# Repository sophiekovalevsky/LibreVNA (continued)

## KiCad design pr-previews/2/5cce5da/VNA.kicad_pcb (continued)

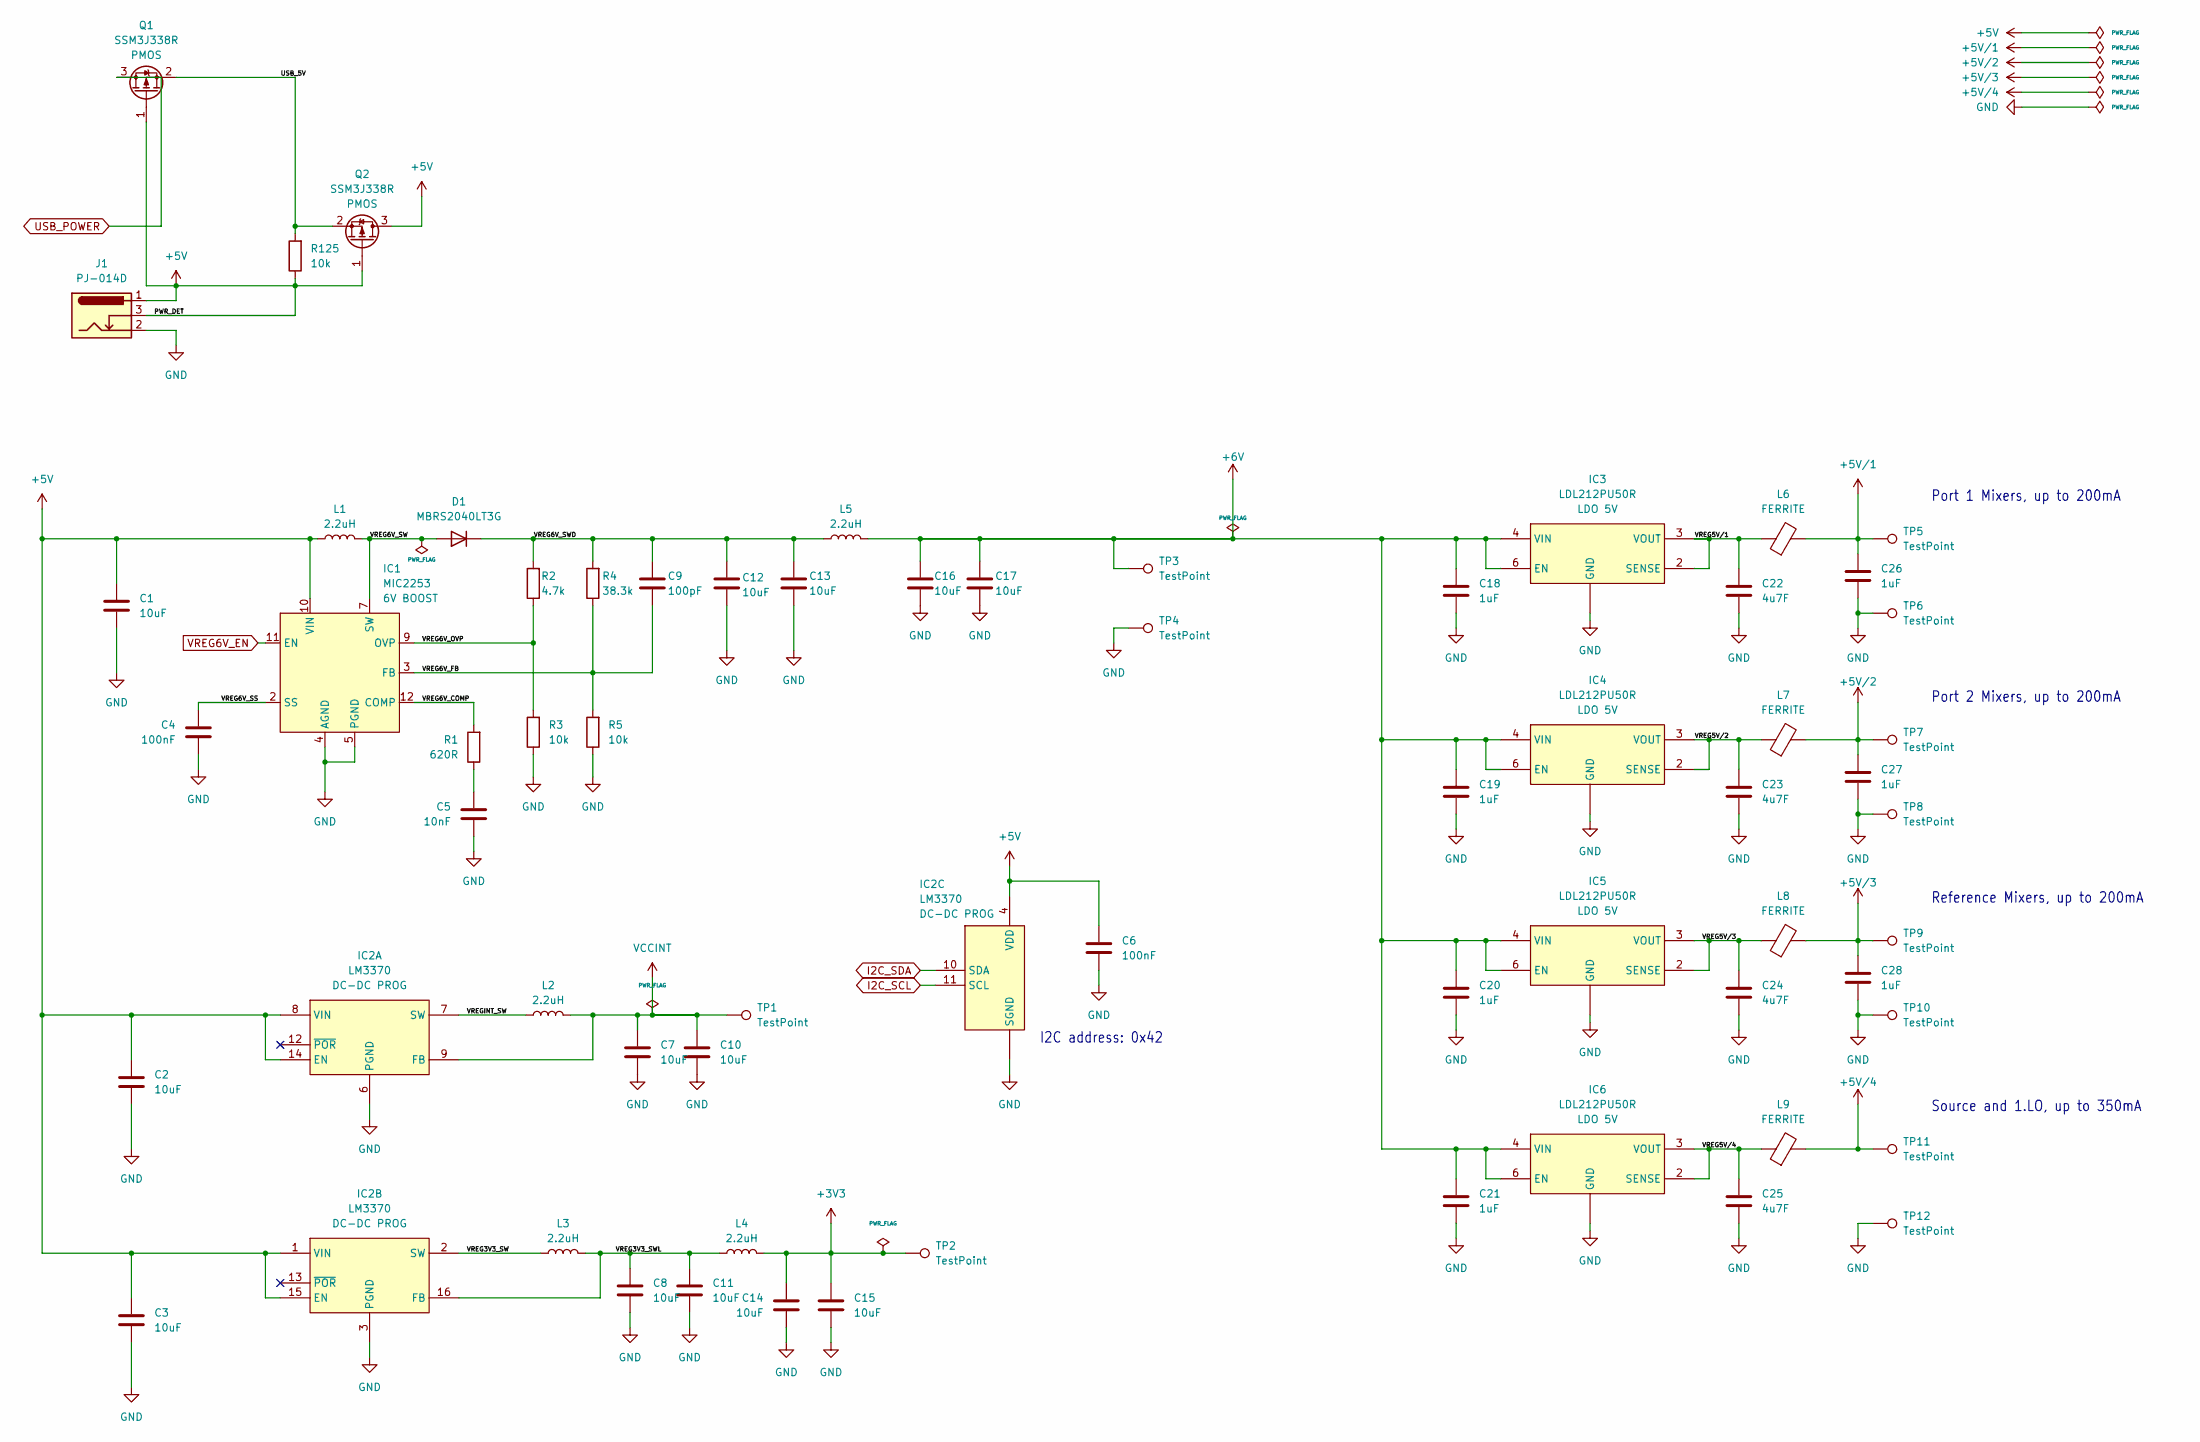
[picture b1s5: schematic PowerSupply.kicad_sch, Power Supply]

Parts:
C1, C2, C3, C7, C8, C10, C11, C12, C13, C14, C15, C16, C17: 10uF; C_1206_3216Metric
C4, C6: 100nF; C_0402_1005Metric
C5: 10nF; C_0402_1005Metric
C9: 100pF; C_0402_1005Metric
C18, C19, C20, C21, C26, C27, C28: 1uF; C_0603_1608Metric
C22, C23, C24, C25: 4u7F; C_0603_1608Metric
D1: MBRS2040LT3G; D_SMB; MPN MBRS2040LT3G
IC1: MIC2253; DFN-12-1EP_3x3mm_P0.45mm_EP1.66x2.38mm; MPN MIC2253-06YML
IC2: LM3370; DFN-16-1EP_4x5mm_P0.5mm_EP2.44x4.34mm; MPN LM3370SD-3021
IC3, IC4, IC5, IC6: LDL212PU50R; WSON-6-1EP_3x3mm_P0.95mm; MPN LDL212PU50R
J1: PJ-014D; MPN PJ-014D
L1, L2, L3, L4, L5: 2.2uH; L_Sunlord_SWPA5040S; MPN SRN5040-2R2Y
L6, L7, L8, L9: FERRITE; R_0402_1005Metric; MPN BLM15AX601SN1
Q1, Q2: SSM3J338R; SOT-23; MPN SSM3J338R
R1: 620R; R_0402_1005Metric
R2: 4.7k; R_0402_1005Metric
R3, R5, R125: 10k; R_0402_1005Metric
R4: 38.3k; R_0402_1005Metric
TP1, TP2, TP3, TP4, TP5, TP6, TP7, TP8, TP9, TP10, TP11, TP12: TestPoint; B1,27

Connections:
+3V3: C14.1, C15.1, L4.2, TP2.1; also elsewhere on the board
+5V/1: C26.2, L6.2, TP5.1; also elsewhere on the board
+5V/2: C27.2, L7.2, TP7.1; also elsewhere on the board
+5V/3: C28.2, L8.2, TP9.1; also elsewhere on the board
+5V/4: L9.2, TP11.1; also elsewhere on the board
+6V: C16.1, C17.1, C18.2, C19.2, C20.2, C21.2, IC3.4 (VIN), IC3.6 (EN), IC4.4 (VIN), IC4.6 (EN), IC5.4 (VIN), IC5.6 (EN), IC6.4 (VIN), IC6.6 (EN), L5.2, TP3.1
/Power Supply/USB_5V: Q1.2 (S), Q2.2 (S), R125.2
/Power Supply/VREG3V3_SW: IC2.2 (SW), L3.1
/Power Supply/VREG3V3_SWL: C8.1, C11.1, IC2.16 (FB), L3.2, L4.1
/Power Supply/VREG5V/1: C22.2, IC3.2 (SENSE), IC3.3 (VOUT), L6.1
/Power Supply/VREG5V/2: C23.2, IC4.2 (SENSE), IC4.3 (VOUT), L7.1
/Power Supply/VREG5V/3: C24.2, IC5.2 (SENSE), IC5.3 (VOUT), L8.1
/Power Supply/VREG5V/4: C25.2, IC6.2 (SENSE), IC6.3 (VOUT), L9.1
/Power Supply/VREG6V_COMP: IC1.12 (COMP), R1.2
/Power Supply/VREG6V_FB: C9.2, IC1.3 (FB), R4.1, R5.2
/Power Supply/VREG6V_OVP: IC1.9 (OVP), R2.1, R3.2
/Power Supply/VREG6V_SS: C4.2, IC1.2 (SS)
/Power Supply/VREG6V_SW: D1.2 (A), IC1.7 (SW), IC1.8 (SW), L1.2
/Power Supply/VREG6V_SWD: C9.1, C12.1, C13.1, D1.1 (K), L5.1, R2.2, R4.2
/Power Supply/VREGINT_SW: IC2.7 (SW), L2.1
GND: C1.2, C2.2, C3.2, C4.1, C5.1, C6.1, C7.2, C8.2, C10.2, C11.2, C12.2, C13.2, C14.2, C15.2, C16.2, C17.2, C18.1, C19.1, C20.1, C21.1, C22.1, C23.1, C24.1, C25.1, C26.1, C27.1, C28.1, IC1.4 (AGND), IC1.5 (PGND), IC1.6 (PGND), IC1.13 (PGND), IC2.3 (PGND), IC2.5 (SGND), IC2.6 (PGND), IC2.17 (SGND), IC3.1 (GND), IC3.7 (GND), IC4.1 (GND), IC4.7 (GND), IC5.1 (GND), IC5.7 (GND), IC6.1 (GND), IC6.7 (GND), J1.2, R3.1, R5.1, TP4.1, TP6.1, TP8.1, TP10.1, TP12.1; also elsewhere on the board
I2C_SCL: IC2.11 (SCL); also elsewhere on the board
I2C_SDA: IC2.10 (SDA); also elsewhere on the board
unnamed: C5.2, R1.1
USB_POWER: Q1.3 (D); also elsewhere on the board
VCCINT: C7.1, C10.1, IC2.9 (FB), L2.2, TP1.1; also elsewhere on the board
VREG6V_EN: IC1.11 (EN); also elsewhere on the board

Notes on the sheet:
Port 2 Mixers, up to 200mA
Source and 1.LO, up to 350mA
I2C address: 0x42
Port 1 Mixers, up to 200mA
Reference Mixers, up to 200mA

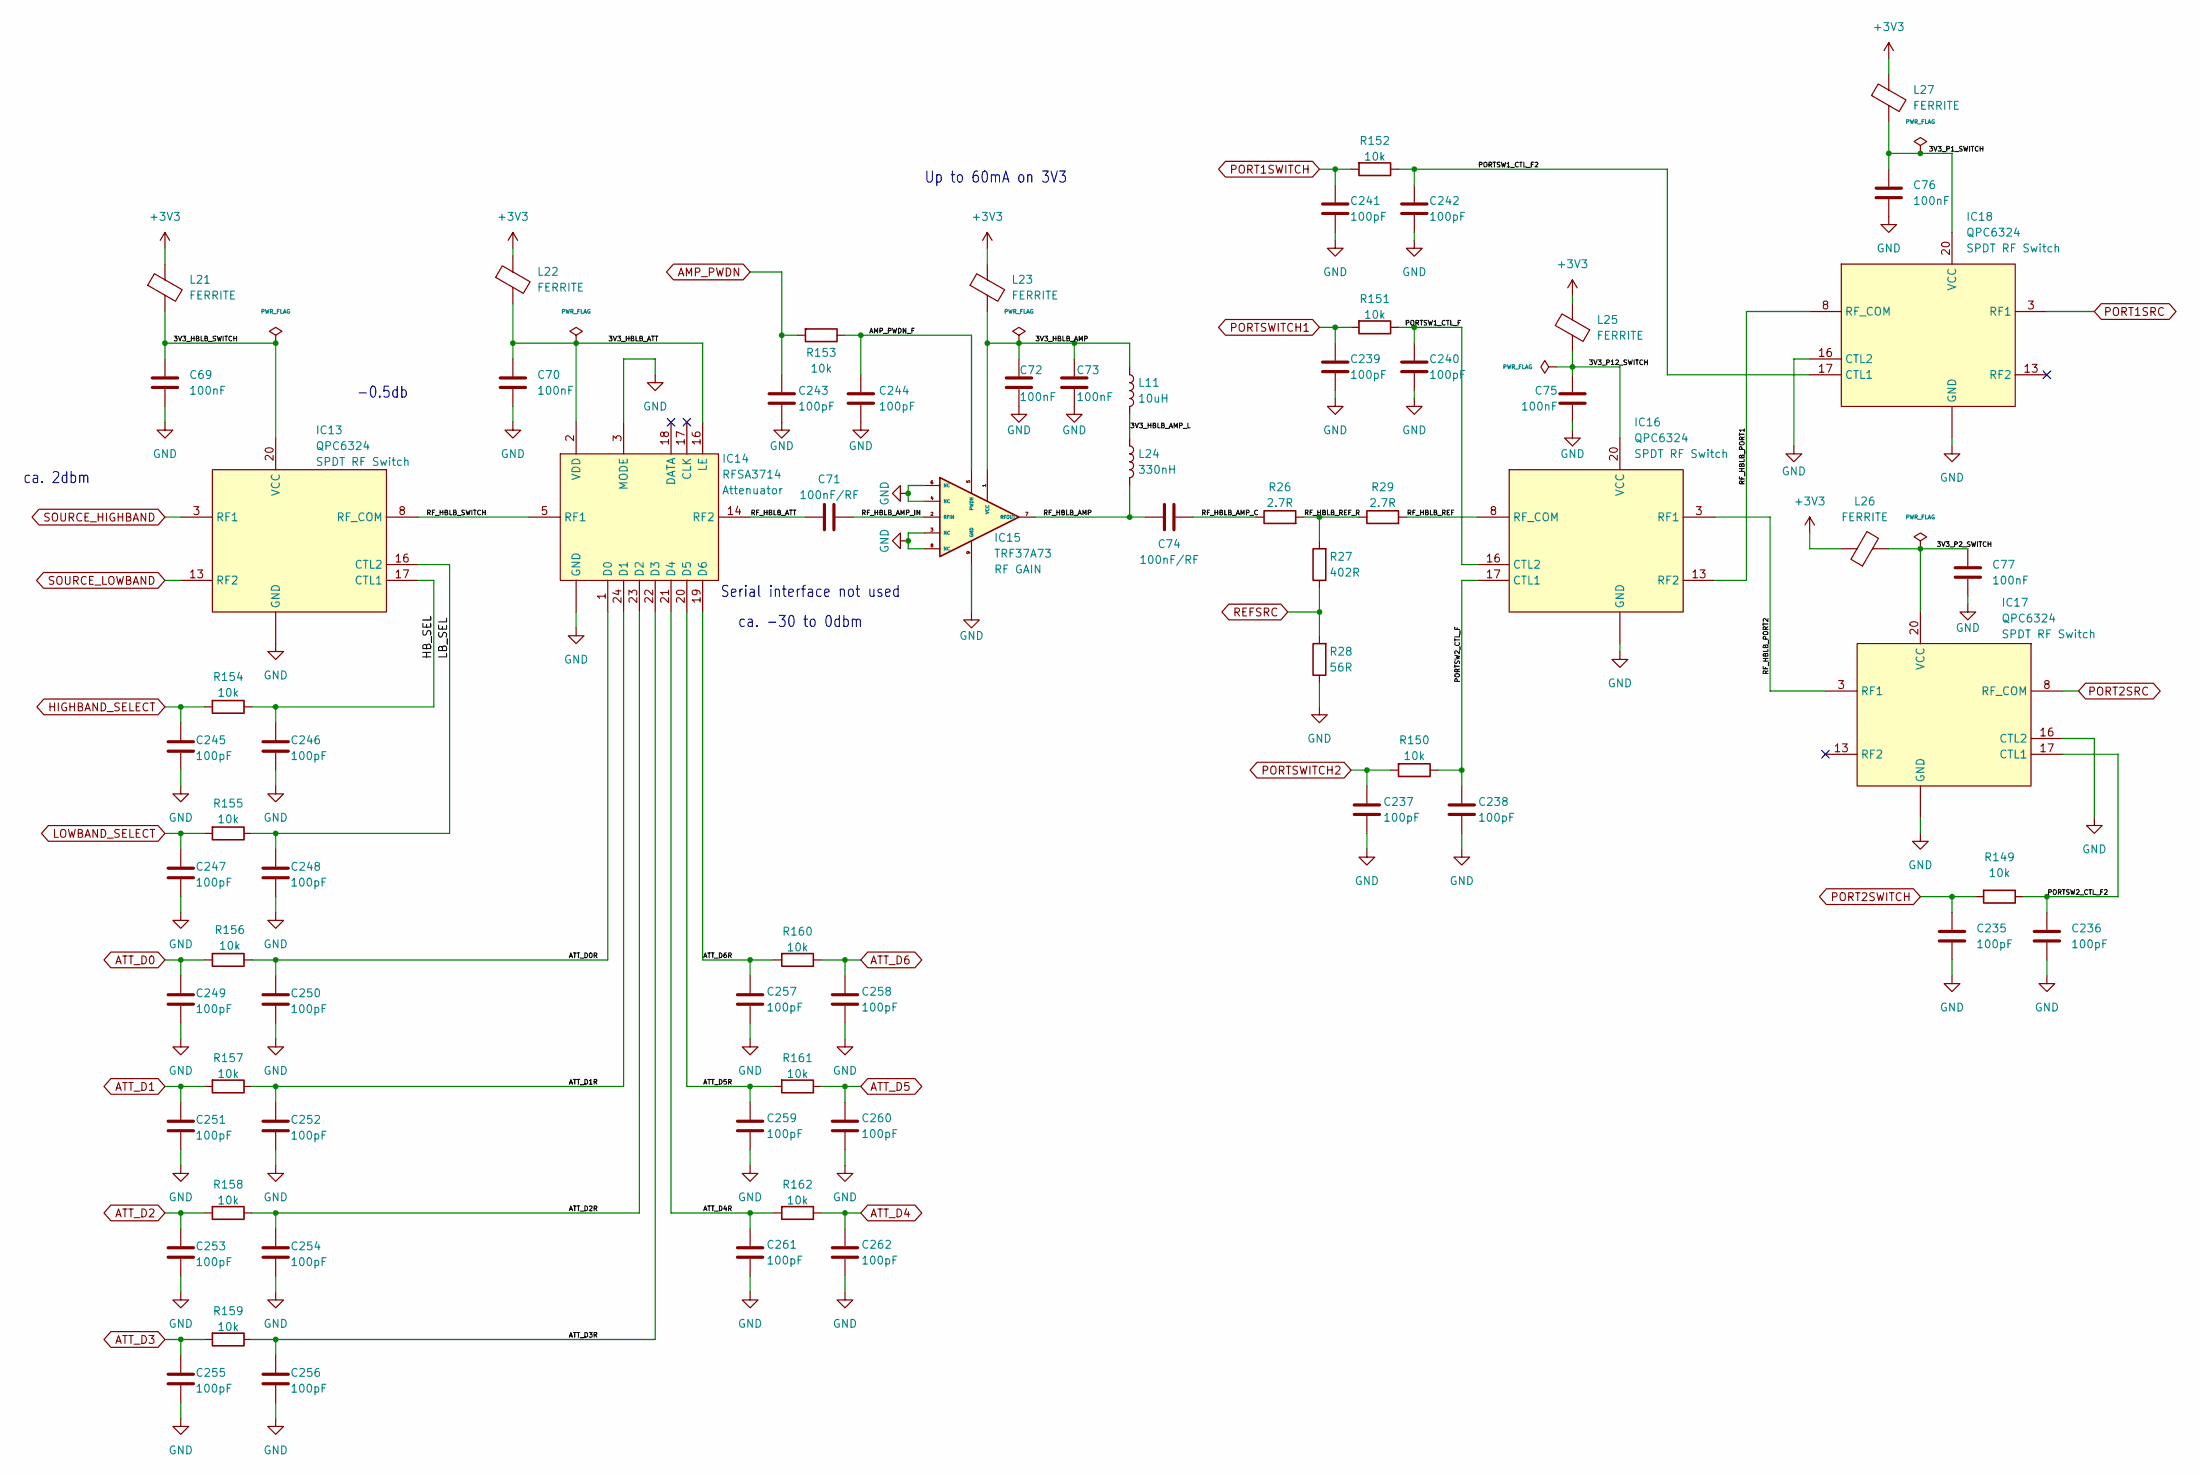
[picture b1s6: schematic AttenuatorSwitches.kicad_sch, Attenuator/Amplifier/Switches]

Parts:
C69, C70, C72, C73, C75, C76, C77: 100nF; C_0402_1005Metric
C71, C74: 100nF/RF; C_0402_1005Metric
C235, C236, C237, C238, C239, C240, C241, C242, C243, C244, C245, C246, C247, C248, C249, C250, C251, C252, C253, C254, C255, C256, C257, C258, C259, C260, C261, C262: 100pF; C_0402_1005Metric
IC13, IC16, IC17, IC18: QPC6324; QFN-20-1EP_4x4mm_P0.5mm_EP2.5x2.5mm; MPN QPC6324SR
IC14: RFSA3714; QFN-24-1EP_4x4mm_P0.5mm_EP2.6x2.6mm; MPN RFSA3714TR13
IC15: TRF37A73; DFN-8-1EP_2x2mm_P0.5mm_EP0.9x1.6mm; MPN TRF37A73IDSGR
L11: 10uH; L_0805_2012Metric_Pad1.15x1.40mm_HandSolder
L21, L22, L23, L25, L26, L27: FERRITE; R_0402_1005Metric; MPN BLM15AX601SN1
L24: 330nH; L_0402_1005Metric; MPN LQW15CNR33J10D
R26, R29: 2.7R; R_0402_1005Metric
R27: 402R; R_0402_1005Metric
R28: 56R; R_0402_1005Metric
R149, R150, R151, R152, R153, R154, R155, R156, R157, R158, R159, R160, R161, R162: 10k; R_0402_1005Metric

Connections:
+3V3: L21.1, L22.1, L23.1, L25.2, L26.1, L27.1; also elsewhere on the board
/Attenuator Amp Switches/3V3_HBLB_AMP: C72.1, C73.1, IC15.1 (VCC), L11.1, L23.2
/Attenuator Amp Switches/3V3_HBLB_AMP_L: L11.2, L24.1
/Attenuator Amp Switches/3V3_HBLB_ATT: C70.1, IC14.2 (VDD), IC14.16 (LE), L22.2
/Attenuator Amp Switches/3V3_HBLB_SWITCH: C69.1, IC13.20 (VCC), L21.2
/Attenuator Amp Switches/3V3_P1_SWITCH: C76.1, IC18.20 (VCC), L27.2
/Attenuator Amp Switches/3V3_P2_SWITCH: C77.1, IC17.20 (VCC), L26.2
/Attenuator Amp Switches/3V3_P12_SWITCH: C75.1, IC16.20 (VCC), L25.1
/Attenuator Amp Switches/AMP_PWDN_F: C244.1, IC15.5 (PWDN), R153.1
/Attenuator Amp Switches/ATT_D0R: C250.1, IC14.1 (D0), R156.1
/Attenuator Amp Switches/ATT_D1R: C252.1, IC14.24 (D1), R157.1
/Attenuator Amp Switches/ATT_D2R: C254.1, IC14.23 (D2), R158.1
/Attenuator Amp Switches/ATT_D3R: C256.1, IC14.22 (D3), R159.1
/Attenuator Amp Switches/ATT_D4R: C261.1, IC14.21 (D4), R162.2
/Attenuator Amp Switches/ATT_D5R: C259.1, IC14.20 (D5), R161.2
/Attenuator Amp Switches/ATT_D6R: C257.1, IC14.19 (D6), R160.2
/Attenuator Amp Switches/HB_SEL: C246.1, IC13.17 (CTL1), R154.1
/Attenuator Amp Switches/LB_SEL: C248.1, IC13.16 (CTL2), R155.1
/Attenuator Amp Switches/PORTSW1_CTL_F: C240.1, IC16.16 (CTL2), R151.1
/Attenuator Amp Switches/PORTSW1_CTL_F2: C242.1, IC18.17 (CTL1), R152.1
/Attenuator Amp Switches/PORTSW2_CTL_F: C238.1, IC16.17 (CTL1), R150.1
/Attenuator Amp Switches/PORTSW2_CTL_F2: C236.1, IC17.17 (CTL1), R149.1
/Attenuator Amp Switches/RF_HBLB_AMP: C74.1, IC15.7 (RFOUT), L24.2
/Attenuator Amp Switches/RF_HBLB_AMP_C: C74.2, R26.1
/Attenuator Amp Switches/RF_HBLB_AMP_IN: C71.2, IC15.2 (RFIN)
/Attenuator Amp Switches/RF_HBLB_ATT: C71.1, IC14.14 (RF2)
/Attenuator Amp Switches/RF_HBLB_PORT1: IC16.13 (RF2), IC18.8 (RF_COM)
/Attenuator Amp Switches/RF_HBLB_PORT2: IC16.3 (RF1), IC17.3 (RF1)
/Attenuator Amp Switches/RF_HBLB_REF: IC16.8 (RF_COM), R29.2
/Attenuator Amp Switches/RF_HBLB_REF_R: R26.2, R27.2, R29.1
/Attenuator Amp Switches/RF_HBLB_SWITCH: IC13.8 (RF_COM), IC14.5 (RF1)
AMP_PWDN: C243.1, R153.2; also elsewhere on the board
ATT_D0: C249.1, R156.2; also elsewhere on the board
ATT_D1: C251.1, R157.2; also elsewhere on the board
ATT_D2: C253.1, R158.2; also elsewhere on the board
ATT_D3: C255.1, R159.2; also elsewhere on the board
ATT_D4: C262.1, R162.1; also elsewhere on the board
ATT_D5: C260.1, R161.1; also elsewhere on the board
ATT_D6: C258.1, R160.1; also elsewhere on the board
GND: C69.2, C70.2, C72.2, C73.2, C75.2, C76.2, C77.2, C235.2, C236.2, C237.2, C238.2, C239.2, C240.2, C241.2, C242.2, C243.2, C244.2, C245.2, C246.2, C247.2, C248.2, C249.2, C250.2, C251.2, C252.2, C253.2, C254.2, C255.2, C256.2, C257.2, C258.2, C259.2, C260.2, C261.2, C262.2, IC13.1 (GND), IC13.2 (GND), IC13.4 (GND), IC13.5 (GND), IC13.6 (GND), IC13.7 (GND), IC13.9 (GND), IC13.10 (GND), IC13.11 (GND), IC13.12 (GND), IC13.14 (GND), IC13.15 (GND), IC13.18 (GND), IC13.19 (GND), IC13.21 (GND), IC14.3 (MODE), IC14.4 (GND), IC14.6 (GND), IC14.7 (GND), IC14.8 (GND), IC14.9 (GND), IC14.10 (GND), IC14.11 (GND), IC14.12 (GND), IC14.13 (GND), IC14.15 (GND), IC14.25 (GND), IC15.3 (NC), IC15.4 (NC), IC15.6 (NC), IC15.8 (NC), IC15.9 (GND), IC16.1 (GND), IC16.2 (GND), IC16.4 (GND), IC16.5 (GND), IC16.6 (GND), IC16.7 (GND), IC16.9 (GND), IC16.10 (GND), IC16.11 (GND), IC16.12 (GND), IC16.14 (GND), IC16.15 (GND), IC16.18 (GND), IC16.19 (GND), IC16.21 (GND), IC17.1 (GND), IC17.2 (GND), IC17.4 (GND), IC17.5 (GND), IC17.6 (GND), IC17.7 (GND), IC17.9 (GND), IC17.10 (GND), IC17.11 (GND), IC17.12 (GND), IC17.14 (GND), IC17.15 (GND), IC17.16 (CTL2), IC17.18 (GND), IC17.19 (GND), IC17.21 (GND), IC18.1 (GND), IC18.2 (GND), IC18.4 (GND), IC18.5 (GND), IC18.6 (GND), IC18.7 (GND), IC18.9 (GND), IC18.10 (GND), IC18.11 (GND), IC18.12 (GND), IC18.14 (GND), IC18.15 (GND), IC18.16 (CTL2), IC18.18 (GND), IC18.19 (GND), IC18.21 (GND), R28.1; also elsewhere on the board
HIGHBAND_SELECT: C245.1, R154.2; also elsewhere on the board
LOWBAND_SELECT: C247.1, R155.2; also elsewhere on the board
PORT1SRC: IC18.3 (RF1); also elsewhere on the board
PORT1SWITCH: C241.1, R152.2; also elsewhere on the board
PORT2SRC: IC17.8 (RF_COM); also elsewhere on the board
PORT2SWITCH: C235.1, R149.2; also elsewhere on the board
PORTSWITCH1: C239.1, R151.2; also elsewhere on the board
PORTSWITCH2: C237.1, R150.2; also elsewhere on the board
REFSRC: R27.1, R28.2; also elsewhere on the board
SOURCE_HIGHBAND: IC13.3 (RF1); also elsewhere on the board
SOURCE_LOWBAND: IC13.13 (RF2); also elsewhere on the board

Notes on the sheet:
ca. 2dbm
-0.5db
Up to 60mA on 3V3
ca. -30 to 0dbm
Serial interface not used

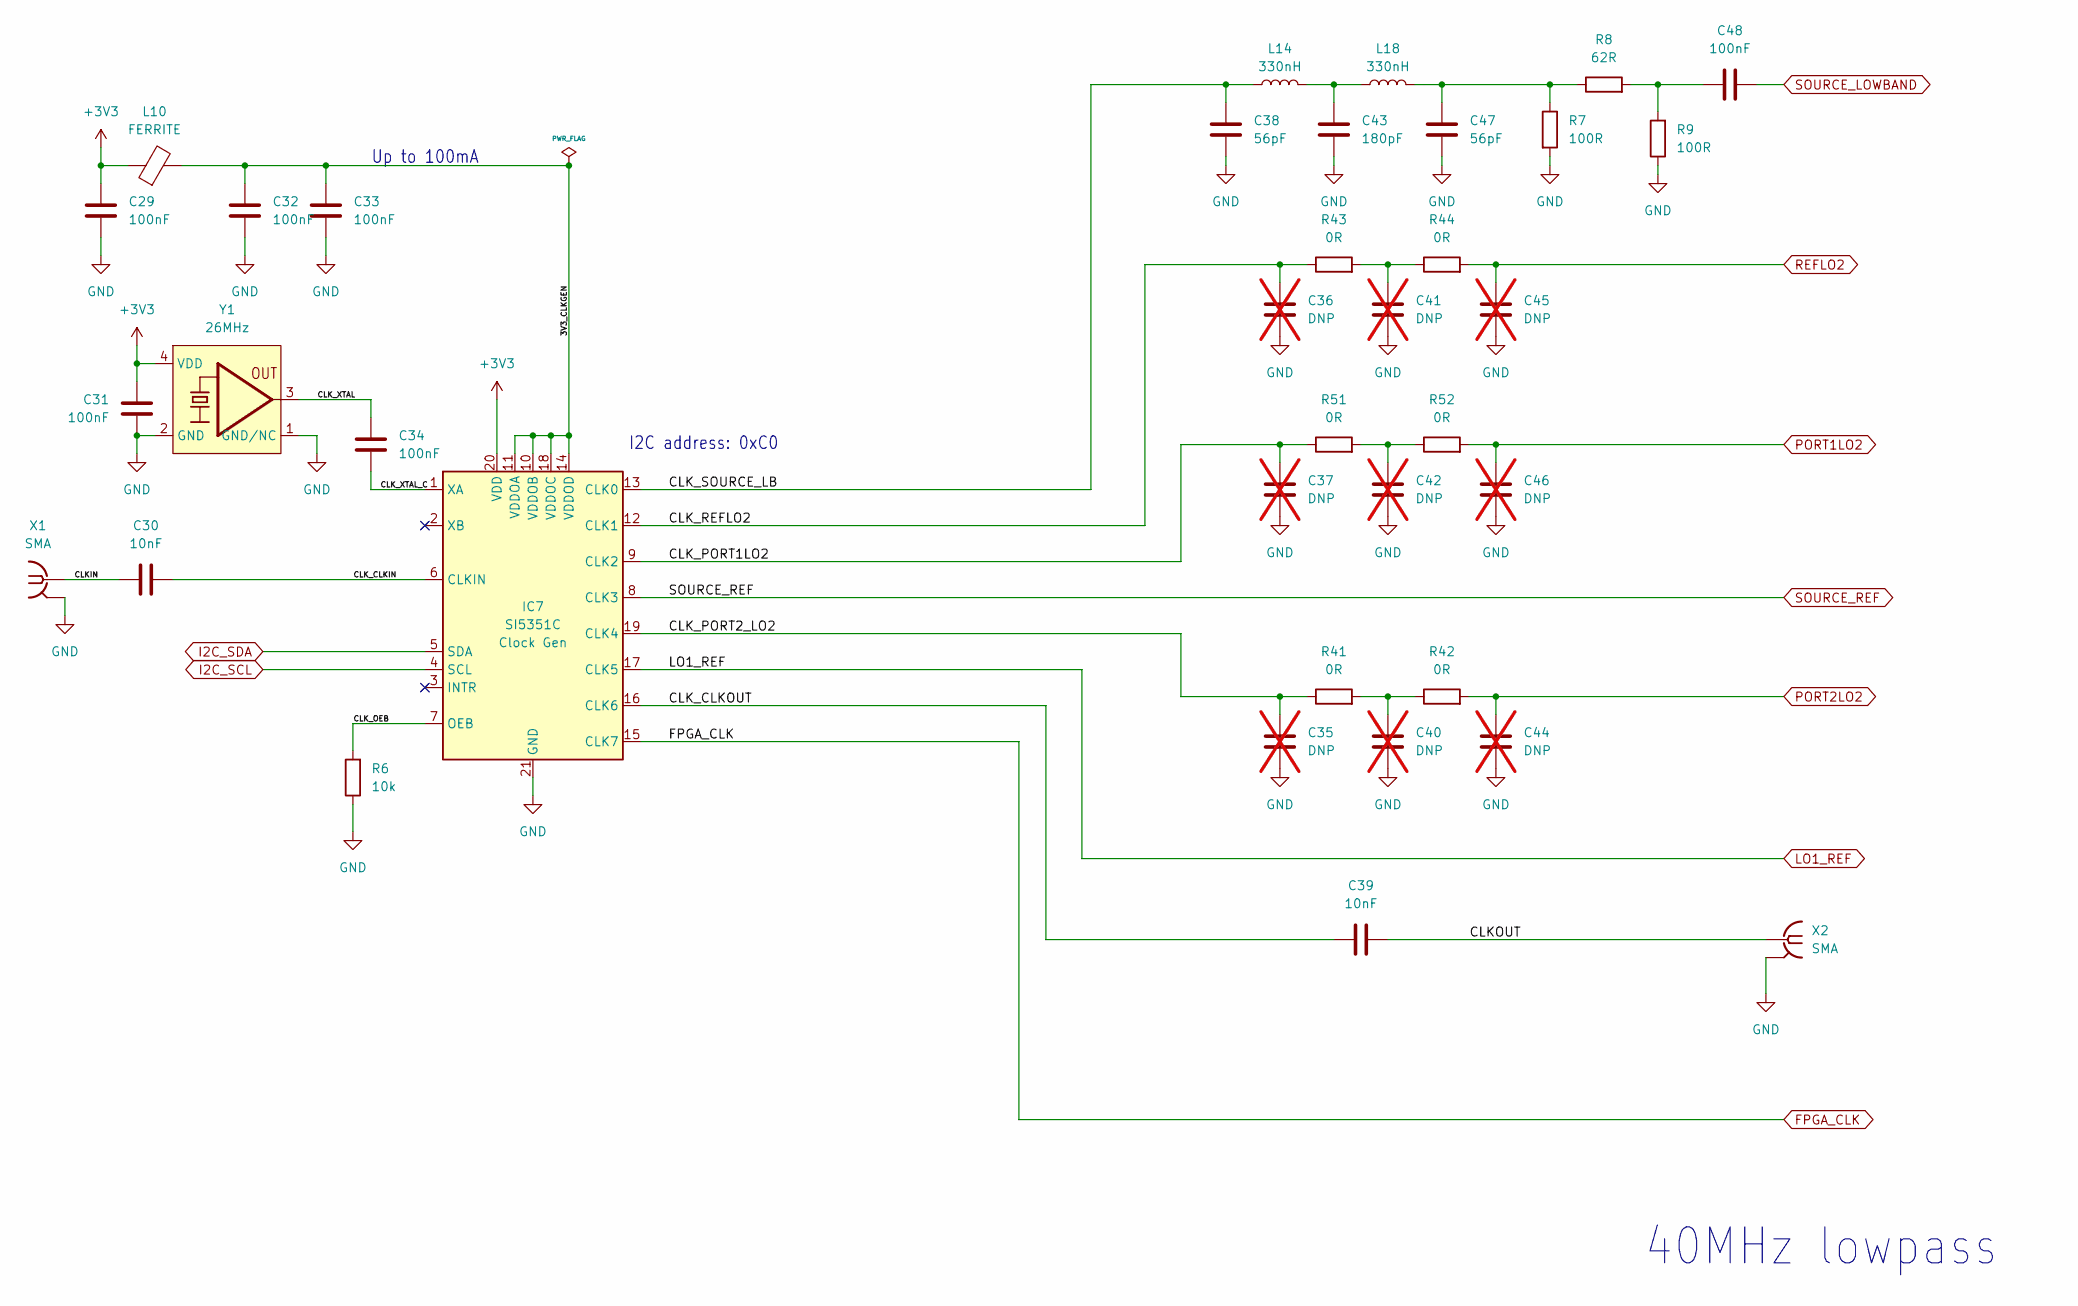
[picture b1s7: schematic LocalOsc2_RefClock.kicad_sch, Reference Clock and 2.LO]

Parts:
C29, C31, C32, C33, C34, C48: 100nF; C_0402_1005Metric
C30, C39: 10nF; C_0402_1005Metric
C35, C36, C37, C40, C41, C42, C44, C45, C46: DNP; C_0402_1005Metric; not fitted
C38, C47: 56pF; C_0402_1005Metric
C43: 180pF; C_0402_1005Metric
IC7: SI5351C; QFN-20-1EP_4x4mm_P0.5mm_EP2.7x2.7mm; MPN SI5351C-B-GM
L10: FERRITE; R_0402_1005Metric; MPN BLM15AX601SN1
L14, L18: 330nH; L_0402_1005Metric; MPN LQW15CNR33J10D
R6: 10k; R_0402_1005Metric
R7, R9: 100R; R_0402_1005Metric
R8: 62R; R_0402_1005Metric
R41, R42, R43, R44, R51, R52: 0R; R_0402_1005Metric
X1, X2: SMA; J502-ND-142-0711-821_826
Y1: 26MHz; Oscillator_SMD_ECS_20CSMV4_2.0x1.6mm; MPN ECS-TXO-20CSMV4-260-AN-TR

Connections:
+3V3: C29.2, C31.2, IC7.20 (VDD), L10.1, Y1.4 (VDD); also elsewhere on the board
/2.LO + Ref Clock/3V3_CLKGEN: C32.2, C33.2, IC7.10 (VDDOB), IC7.11 (VDDOA), IC7.14 (VDDOD), IC7.18 (VDDOC), L10.2
/2.LO + Ref Clock/CLKIN: C30.1, X1.1
/2.LO + Ref Clock/CLKOUT: C39.2, X2.1
/2.LO + Ref Clock/CLK_CLKIN: C30.2, IC7.6 (CLKIN)
/2.LO + Ref Clock/CLK_CLKOUT: C39.1, IC7.16 (CLK6)
/2.LO + Ref Clock/CLK_OEB: IC7.7 (OEB), R6.2
/2.LO + Ref Clock/CLK_PORT1LO2: C37.1, IC7.9 (CLK2), R51.1
/2.LO + Ref Clock/CLK_PORT2_LO2: C35.1, IC7.19 (CLK4), R41.1
/2.LO + Ref Clock/CLK_REFLO2: C36.1, IC7.12 (CLK1), R43.1
/2.LO + Ref Clock/CLK_SOURCE_LB: C38.1, IC7.13 (CLK0), L14.1
/2.LO + Ref Clock/CLK_XTAL: C34.2, Y1.3 (OUT)
/2.LO + Ref Clock/CLK_XTAL_C: C34.1, IC7.1 (XA)
FPGA_CLK: IC7.15 (CLK7); also elsewhere on the board
GND: C29.1, C31.1, C32.1, C33.1, C35.2, C36.2, C37.2, C38.2, C40.2, C41.2, C42.2, C43.2, C44.2, C45.2, C46.2, C47.2, IC7.21 (GND), R6.1, R7.2, R9.1, X1.G@1 (2), X1.G@2 (2), X1.G@3 (2), X1.G@4 (2), X2.G@1 (2), X2.G@2 (2), X2.G@3 (2), X2.G@4 (2), Y1.1 (GND/NC), Y1.2 (GND); also elsewhere on the board
I2C_SCL: IC7.4 (SCL); also elsewhere on the board
I2C_SDA: IC7.5 (SDA); also elsewhere on the board
LO1_REF: IC7.17 (CLK5); also elsewhere on the board
unnamed: C40.1, R41.2, R42.1
unnamed: C41.1, R43.2, R44.1
unnamed: C42.1, R51.2, R52.1
unnamed: C43.1, L14.2, L18.1
unnamed: C47.1, L18.2, R7.1, R8.1
unnamed: C48.2, R8.2, R9.2
PORT1LO2: C46.1, R52.2; also elsewhere on the board
PORT2LO2: C44.1, R42.2; also elsewhere on the board
REFLO2: C45.1, R44.2; also elsewhere on the board
SOURCE_LOWBAND: C48.1; also elsewhere on the board
SOURCE_REF: IC7.8 (CLK3); also elsewhere on the board

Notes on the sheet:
I2C address: 0xC0
40MHz lowpass
Up to 100mA

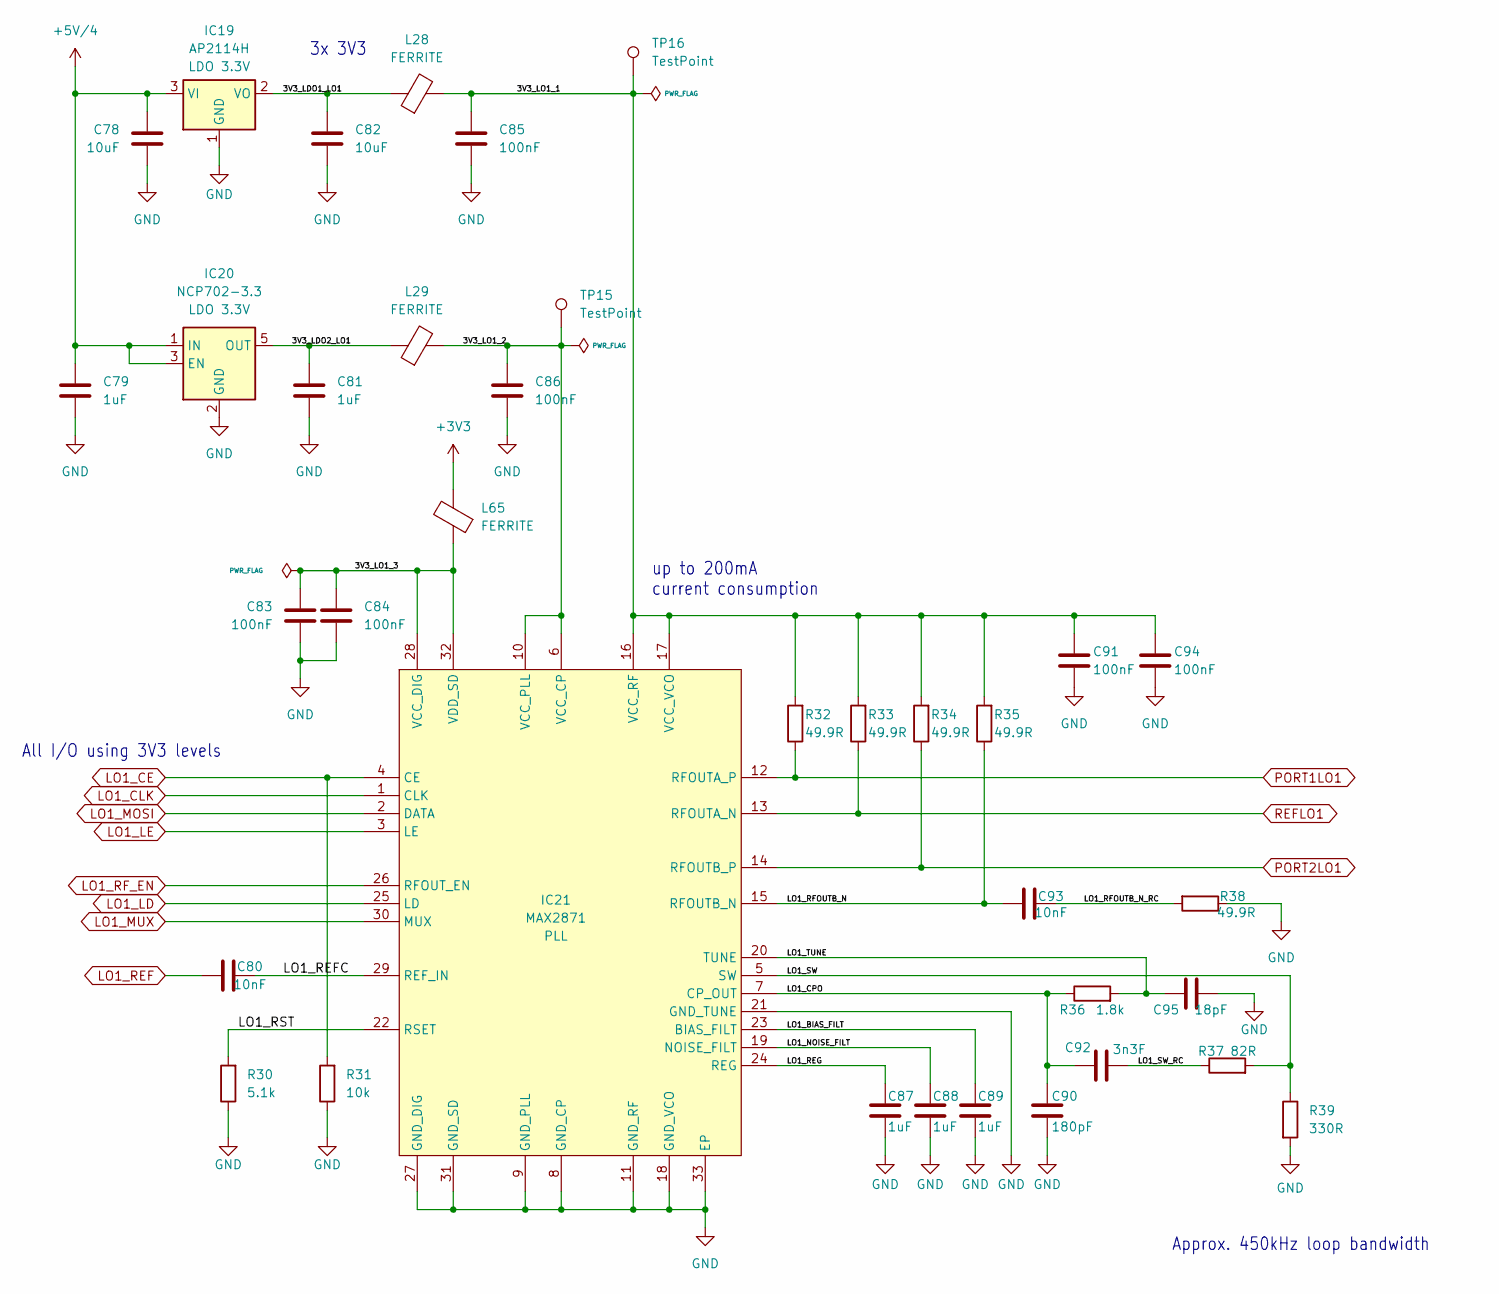
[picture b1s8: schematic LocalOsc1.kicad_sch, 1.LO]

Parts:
C78, C82: 10uF; C_1206_3216Metric
C79, C81: 1uF; C_0603_1608Metric
C80, C93: 10nF; C_0402_1005Metric
C83, C84, C85, C86, C91, C94: 100nF; C_0402_1005Metric
C87, C88, C89: 1uF; C_0402_1005Metric
C90: 180pF; C_0402_1005Metric
C92: 3n3F; C_0402_1005Metric
C95: 18pF; C_0402_1005Metric
IC19: AP2114H; SOT-223-3_TabPin2; MPN AP2114H-3.3TRG1
IC20: NCP702-3.3; SOT-23-5; MPN NCP702SN33T1G
IC21: MAX2871; QFN-32-1EP_5x5mm_P0.5mm_EP3.1x3.1mm; MPN MAX2871ETJ+
L28, L29, L65: FERRITE; R_0402_1005Metric; MPN BLM15AX601SN1
R30: 5.1k; R_0402_1005Metric
R31: 10k; R_0402_1005Metric
R32, R33, R34, R35, R38: 49.9R; R_0402_1005Metric
R36: 1.8k; R_0402_1005Metric
R37: 82R; R_0402_1005Metric
R39: 330R; R_0402_1005Metric
TP15, TP16: TestPoint; B1,27

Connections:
+3V3: L65.2; also elsewhere on the board
+5V/4: C78.1, C79.1, IC19.3 (VI), IC20.1 (IN), IC20.3 (EN); also elsewhere on the board
/1.LO/3V3_LDO1_LO1: C82.1, IC19.2 (VO), L28.1
/1.LO/3V3_LDO2_LO1: C81.1, IC20.5 (OUT), L29.1
/1.LO/3V3_LO1_1: C85.1, C91.1, C94.1, IC21.16 (VCC_RF), IC21.17 (VCC_VCO), L28.2, R32.2, R33.2, R34.2, R35.2, TP16.1
/1.LO/3V3_LO1_2: C86.1, IC21.6 (VCC_CP), IC21.10 (VCC_PLL), L29.2, TP15.1
/1.LO/3V3_LO1_3: C83.1, C84.1, IC21.28 (VCC_DIG), IC21.32 (VDD_SD), L65.1
/1.LO/LO1_BIAS_FILT: C89.1, IC21.23 (BIAS_FILT)
/1.LO/LO1_CPO: C90.1, C92.2, IC21.7 (CP_OUT), R36.1
/1.LO/LO1_NOISE_FILT: C88.1, IC21.19 (NOISE_FILT)
/1.LO/LO1_REFC: C80.2, IC21.29 (REF_IN)
/1.LO/LO1_REG: C87.1, IC21.24 (REG)
/1.LO/LO1_RFOUTB_N: C93.2, IC21.15 (RFOUTB_N), R35.1
/1.LO/LO1_RFOUTB_N_RC: C93.1, R38.2
/1.LO/LO1_RST: IC21.22 (RSET), R30.2
/1.LO/LO1_SW: IC21.5 (SW), R37.2, R39.1
/1.LO/LO1_SW_RC: C92.1, R37.1
/1.LO/LO1_TUNE: C95.2, IC21.20 (TUNE), R36.2
GND: C78.2, C79.2, C81.2, C82.2, C83.2, C84.2, C85.2, C86.2, C87.2, C88.2, C89.2, C90.2, C91.2, C94.2, C95.1, IC19.1 (GND), IC20.2 (GND), IC21.8 (GND_CP), IC21.9 (GND_PLL), IC21.11 (GND_RF), IC21.18 (GND_VCO), IC21.21 (GND_TUNE), IC21.27 (GND_DIG), IC21.31 (GND_SD), IC21.33 (EP), R30.1, R31.1, R38.1, R39.2; also elsewhere on the board
LO1_CE: IC21.4 (CE), R31.2; also elsewhere on the board
LO1_CLK: IC21.1 (CLK); also elsewhere on the board
LO1_LD: IC21.25 (LD); also elsewhere on the board
LO1_LE: IC21.3 (LE); also elsewhere on the board
LO1_MOSI: IC21.2 (DATA); also elsewhere on the board
LO1_MUX: IC21.30 (MUX); also elsewhere on the board
LO1_REF: C80.1; also elsewhere on the board
LO1_RF_EN: IC21.26 (RFOUT_EN); also elsewhere on the board
PORT1LO1: IC21.12 (RFOUTA_P), R32.1; also elsewhere on the board
PORT2LO1: IC21.14 (RFOUTB_P), R34.1; also elsewhere on the board
REFLO1: IC21.13 (RFOUTA_N), R33.1; also elsewhere on the board

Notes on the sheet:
All I/O using 3V3 levels
up to 200mA current consumption
3x 3V3
Approx. 450kHz loop bandwidth

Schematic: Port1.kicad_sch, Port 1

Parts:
C96, C99, C109, C110: 100nF/RF; C_0402_1005Metric
C97, C98, C102, C103, C114, C115, C116, C117, C118, C119, C122, C132, C269: 100nF; C_0402_1005Metric
C100, C101, C108, C129, C131: 1uF; C_0402_1005Metric
C104, C105, C106, C111, C120, C123: 10nF; C_0402_1005Metric
C107, C112, C113: DNP; C_0402_1005Metric; not fitted
C121, C125, C126, C127: 330pF; C_0402_1005Metric
C124: 120pF; C_0402_1005Metric
C128: 150pF; C_0402_1005Metric
C130: 33pF; C_0402_1005Metric
IC22: LT5560; WSON-8-1EP_3x3mm_P0.5mm_EP1.45x2.4mm; MPN LT5560EDD
IC23: THS4521IDGKR; VSSOP-8_3.0x3.0mm_P0.65mm; MPN THS4521IDGKR
IC24: ADL5801; QFN-24-1EP_4x4mm_P0.5mm_EP2.6x2.6mm; MPN ADL5801
IC25: NCP702-1.8; SOT-23-5; MPN NCP702SN18T1G
IC26: MCP33131D-10-E/MS; VSSOP-10_3x3mm_P0.5mm; MPN MCP33131D-10-E/MS
J2: SMA; BU-1420701851; MPN AMPHENOL-132289
L12, L13, L15, L16, L17: FERRITE; R_0402_1005Metric; MPN BLM15AX601SN1
L30, L31, L32, L33: 330nH; L_0402_1005Metric; MPN LQW15CNR33J10D
L34, L35: 68nH; L_0402_1005Metric; MPN LQW15AN68NJ00D
L36, L37: 33nH; L_0402_1005Metric; MPN LQW15AN33NJ00D
R45, R46, R50: 49.9R; R_0402_1005Metric
R48: PAT0816-C-3DB-T5; PAT0816; not fitted
R49: PAT0816-C-3DB-T5; PAT0816
R53, R54, R58, R59, R61, R62: 220R; R_0402_1005Metric
R55, R56: 6.8k; R_0402_1005Metric
R57: DNP; R_0402_1005Metric; not fitted
R60: 1k; R_0402_1005Metric
R63, R66: 56R; R_0402_1005Metric
R64, R65: 20R; R_0402_1005Metric
R74, R75: 100R; R_0402_1005Metric
R168: 75R; R_0402_1005Metric
T1: B012-617DB-1-63-B331; EASTEVER_BALUN; MPN B012-617DB-1-63-B331
TP17: TestPoint; B1,27

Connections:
+3V3: C132.2, IC26.9 (SDI), IC26.10 (DVIO); also elsewhere on the board
+5V/1: L12.2, L13.2, L15.2, L16.2, L17.2, R60.1; also elsewhere on the board
/Port 1/RF_PORT1_LO1_C: C269.2, R74.1, R168.2
/Port 1/RF_PORT1_LO1_CR: C114.1, R75.1, R168.1
/Port 1/RF_PORT1_LO1_CRC: C114.2, IC24.3 (LO+)
GND: C97.1, C102.1, C103.1, C104.2, C105.2, C106.2, C108.2, C111.2, C115.1, C116.2, C117.2, C118.1, C119.2, C122.2, C125.1, C127.2, C129.2, C131.2, C132.1, IC22.9 (PGND), IC23.6 (V_{S-}), IC24.1 (GND), IC24.2 (GND), IC24.5 (GND), IC24.6 (GND), IC24.8 (GND), IC24.12 (GND), IC24.14 (GND), IC24.17 (GND), IC24.19 (GND), IC24.23 (GND), IC24.25 (GND), IC25.2 (GND), IC26.5 (GND), J2.G@1 (2), J2.G@2 (2), J2.G@3 (2), J2.G@4 (2), L30.2, L31.2, R48.3, R49.3, R50.2, R74.2, R75.2; also elsewhere on the board
unnamed: C96.2, R49.1
unnamed: C99.1, J2.1
unnamed: C112.2, IC23.5, R55.2, R58.2
unnamed: C113.1, IC23.4, R56.1, R59.2
unnamed: C119.1, C122.1, L16.1, L32.1, L33.1
unnamed: C120.2, C124.1, L34.1
unnamed: C121.1, R58.1, R61.2
unnamed: C121.2, R59.1, R62.2
unnamed: C123.2, C124.2, L35.1
unnamed: C128.1, L34.2, L36.1
unnamed: C128.2, L35.2, L37.1
unnamed: C130.1, L36.2, R63.2, R64.2
unnamed: C130.2, L37.2, R63.1, R65.2
unnamed: IC22.3 (IN+), L30.1, R65.1, R66.2
unnamed: IC22.4 (IN-), L31.1, R64.1, R66.1
unnamed: C98.2, IC22.8 (LO+)
unnamed: C97.2, IC22.1 (LO-)
unnamed: C100.1, IC22.6 (OUT+), R53.2
unnamed: C101.1, IC22.5 (OUT-), R54.2
unnamed: C102.2, C103.2, IC22.7 (VCC), L12.1, R53.1, R54.1
unnamed: C100.2, C112.1, IC23.8 (+), R55.1
unnamed: C101.2, C113.2, IC23.1 (-), R56.2
unnamed: C116.1, IC23.2 (V_{OCM})
unnamed: C115.2, IC23.3 (V_{S+}), L15.1
unnamed: IC24.11 (DETO), R57.2
unnamed: C109.2, IC24.15 (IN+)
unnamed: C110.2, IC24.16 (IN-)
unnamed: C117.1, IC24.4 (LO-)
unnamed: C120.1, IC24.20 (OUT+), L32.2
unnamed: C123.1, IC24.21 (OUT-), L33.2
unnamed: C104.1, C105.1, C106.1, C108.1, C111.1, IC24.7 (VPLO), IC24.13 (VPDT), IC24.18 (VPRF), IC24.24 (VPLO), L17.1
unnamed: C118.2, IC24.10 (VSET), R57.1, R60.2
unnamed: C129.1, IC25.1 (IN), IC25.3 (EN), IC26.1 (VREF), L13.1
unnamed: C131.1, IC25.5 (OUT), IC26.2 (AVDD), TP17.1
unnamed: C125.2, C126.1, IC26.3 (AIN+), R61.1
unnamed: C126.2, C127.1, IC26.4 (AIN-), R62.1
unnamed: R45.2, R46.2, R49.2
unnamed: C107.1, C110.1, T1.3 (IN+)
unnamed: C107.2, C109.1, T1.2 (IN-)
unnamed: R46.1, R50.1, T1.4 (OUT+)
unnamed: C99.2, R45.1, R48.1, R48.2, T1.6 (OUT-)
PORT1LO1: C269.1; also elsewhere on the board
PORT1LO2: C98.1; also elsewhere on the board
PORT1MIX1_EN: IC24.9 (ENBL); also elsewhere on the board
PORT1MIX2_EN: IC22.2 (EN), IC23.7 (~PD); also elsewhere on the board
PORT1SRC: C96.1; also elsewhere on the board
PORT1_CONVSTART: IC26.6 (CONVST); also elsewhere on the board
PORT1_SCLK: IC26.8 (SCLK); also elsewhere on the board
PORT1_SDO: IC26.7 (SDO); also elsewhere on the board

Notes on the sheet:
Downconverter to 1.IF (ca. 250kHz)
(28 Ohm impedance)
-3db pad
Cut wire if attenuator placed
Return loss bridge
Final IF amplifier and ADC driver
P1db: 0dbm
Downconverter to 1.IF (ca. 60MHz)
-10db pad
300kHz lowpass
60MHz lowpass and conversion from 250 Ohm to 28 Ohm impedance
1MS/s ADC
